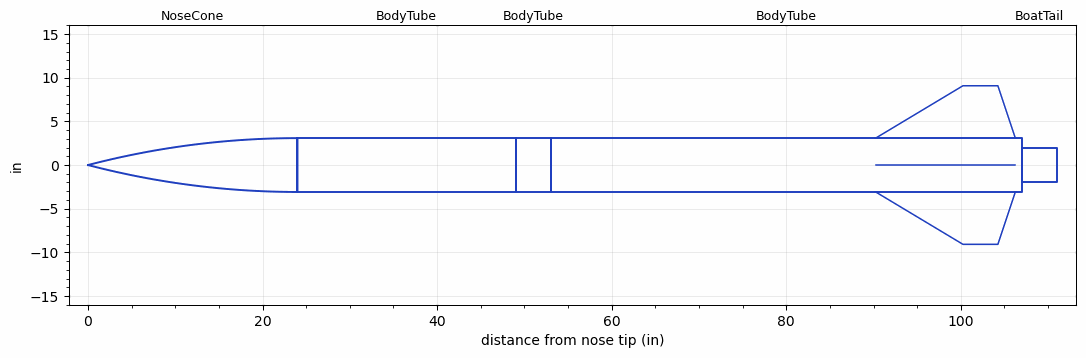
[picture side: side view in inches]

<RASAeroDocument>
 <FileVersion>2</FileVersion>
 <RocketDesign>
  <NoseCone>
   <Length>24</Length>
   <Diameter>6.17</Diameter>
   <Shape>Tangent Ogive</Shape>
   <Location>0</Location>
  </NoseCone>
  <BodyTube>
   <Length>24.9999</Length>
   <Diameter>6.17</Diameter>
   <Location>24</Location>
  </BodyTube>
  <BodyTube>
   <Length>4</Length>
   <Diameter>6.17</Diameter>
   <Location>48.9999</Location>
  </BodyTube>
  <BodyTube>
   <Length>53.9999</Length>
   <Diameter>6.17</Diameter>
   <RailGuideDiameter>0.49</RailGuideDiameter>
   <RailGuideHeight>0.56</RailGuideHeight>
   <Location>52.9999</Location>
   <Fin>
    <Count>4</Count>
    <Chord>16</Chord>
    <Span>6</Span>
    <SweepDistance>10</SweepDistance>
    <TipChord>4</TipChord>
    <Thickness>0.1875</Thickness>
    <Location>16.75</Location>
    <AirfoilSection>Rounded</AirfoilSection>
   </Fin>
  </BodyTube>
  <BoatTail>
   <Length>4</Length>
   <Diameter>4</Diameter>
   <RearDiameter>4</RearDiameter>
   <Location>106.9998</Location>
  </BoatTail>
  <Surface>Polished</Surface>
  <CD>0</CD>
  <ModifiedBarrowman>False</ModifiedBarrowman>
  <Turbulence>False</Turbulence>
  <UseBooster1>False</UseBooster1>
  <UseBooster2>False</UseBooster2>
 </RocketDesign>
 <LaunchSite>
  <Altitude>2500.0001</Altitude>
  <Pressure>27.3253</Pressure>
  <RodAngle>0</RodAngle>
  <RodLength>10</RodLength>
  <Temperature>50.0846</Temperature>
  <WindSpeed>4.4739</WindSpeed>
 </LaunchSite>
 <Recovery>
  <Altitude1>656.168</Altitude1>
  <Altitude2>600</Altitude2>
  <DeviceType1>Parachute</DeviceType1>
  <DeviceType2>Parachute</DeviceType2>
  <Event1>True</Event1>
  <Event2>True</Event2>
  <Size1>18</Size1>
  <Size2>215.9996</Size2>
  <EventType1>Apogee</EventType1>
  <EventType2>Altitude</EventType2>
  <CD1>2.2</CD1>
  <CD2>0</CD2>
 </Recovery>
 <SimulationList>
  <Simulation>
   <SustainerEngine>M2000R  (AT)</SustainerEngine>
   <SustainerLaunchWt>62.3118</SustainerLaunchWt>
   <SustainerCG>66.472</SustainerCG>
   <SustainerIgnitionDelay>0</SustainerIgnitionDelay>
   <Booster1SeparationDelay>0</Booster1SeparationDelay>
   <Booster1IgnitionDelay>0</Booster1IgnitionDelay>
   <IncludeBooster1>False</IncludeBooster1>
   <Booster2Delay>0</Booster2Delay>
   <IncludeBooster2>False</IncludeBooster2>
  </Simulation>
  <Simulation>
   <SustainerEngine>M2500T  (AT)</SustainerEngine>
   <SustainerLaunchWt>60.2772</SustainerLaunchWt>
   <SustainerCG>65.4801</SustainerCG>
   <SustainerIgnitionDelay>0</SustainerIgnitionDelay>
   <Booster1SeparationDelay>0</Booster1SeparationDelay>
   <Booster1IgnitionDelay>0</Booster1IgnitionDelay>
   <IncludeBooster1>False</IncludeBooster1>
   <Booster2Delay>0</Booster2Delay>
   <IncludeBooster2>False</IncludeBooster2>
  </Simulation>
  <Simulation>
   <SustainerEngine>M1939W  (AT)</SustainerEngine>
   <SustainerLaunchWt>62.3147</SustainerLaunchWt>
   <SustainerCG>66.4733</SustainerCG>
   <SustainerIgnitionDelay>0</SustainerIgnitionDelay>
   <Booster1SeparationDelay>0</Booster1SeparationDelay>
   <Booster1IgnitionDelay>0</Booster1IgnitionDelay>
   <IncludeBooster1>False</IncludeBooster1>
   <Booster2Delay>0</Booster2Delay>
   <IncludeBooster2>False</IncludeBooster2>
  </Simulation>
  <Simulation>
   <SustainerEngine>M750W  (AT)</SustainerEngine>
   <SustainerLaunchWt>61.8469</SustainerLaunchWt>
   <SustainerCG>66.2757</SustainerCG>
   <SustainerIgnitionDelay>0</SustainerIgnitionDelay>
   <Booster1SeparationDelay>0</Booster1SeparationDelay>
   <Booster1IgnitionDelay>0</Booster1IgnitionDelay>
   <IncludeBooster1>False</IncludeBooster1>
   <Booster2Delay>0</Booster2Delay>
   <IncludeBooster2>False</IncludeBooster2>
  </Simulation>
  <Simulation>
   <SustainerEngine>M2400T  (AT)</SustainerEngine>
   <SustainerLaunchWt>56.7216</SustainerLaunchWt>
   <SustainerCG>64.5643</SustainerCG>
   <SustainerIgnitionDelay>0</SustainerIgnitionDelay>
   <Booster1SeparationDelay>0</Booster1SeparationDelay>
   <Booster1IgnitionDelay>0</Booster1IgnitionDelay>
   <IncludeBooster1>False</IncludeBooster1>
   <Booster2Delay>0</Booster2Delay>
   <IncludeBooster2>False</IncludeBooster2>
  </Simulation>
  <Simulation>
   <SustainerLaunchWt>57.2304</SustainerLaunchWt>
   <SustainerCG>64.8371</SustainerCG>
   <SustainerIgnitionDelay>0</SustainerIgnitionDelay>
   <Booster1SeparationDelay>0</Booster1SeparationDelay>
   <Booster1IgnitionDelay>0</Booster1IgnitionDelay>
   <IncludeBooster1>False</IncludeBooster1>
   <Booster2Delay>0</Booster2Delay>
   <IncludeBooster2>False</IncludeBooster2>
  </Simulation>
 </SimulationList>
</RASAeroDocument>
